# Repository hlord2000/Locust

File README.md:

# A Cricut Joy control board replacement
Reverse engineered from the 2019 Cricut Joy control board

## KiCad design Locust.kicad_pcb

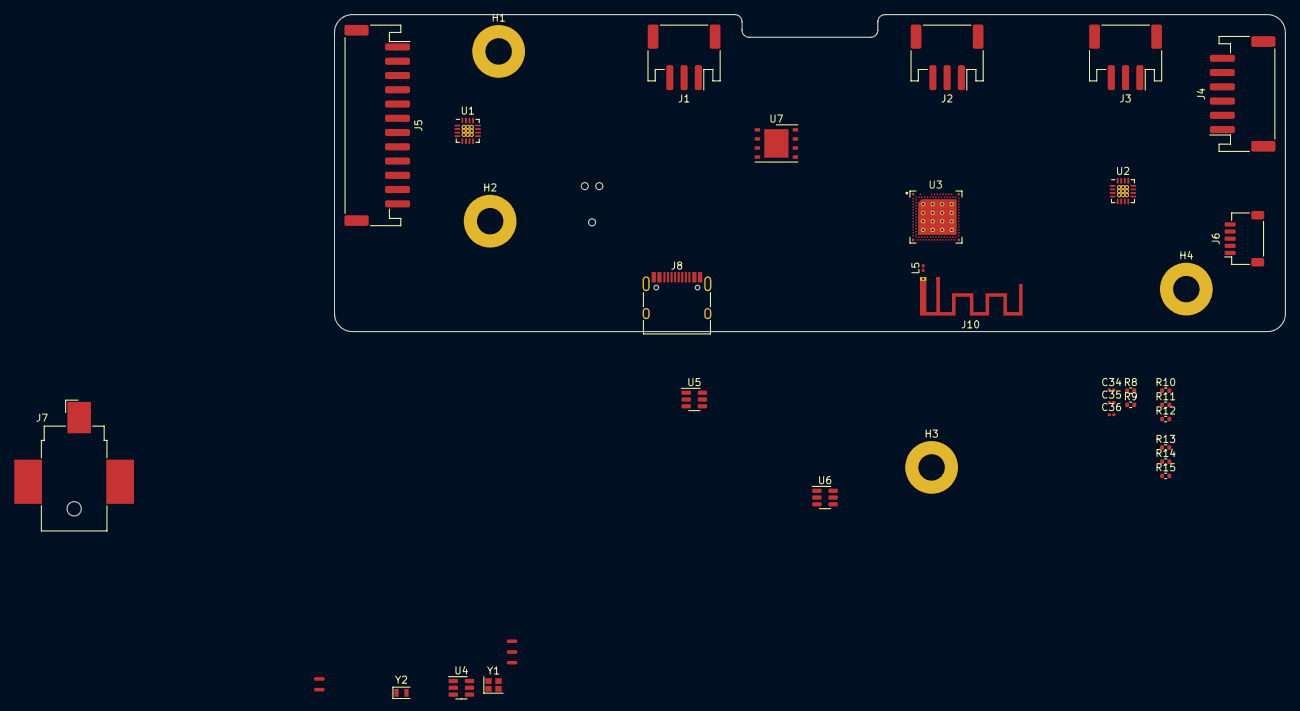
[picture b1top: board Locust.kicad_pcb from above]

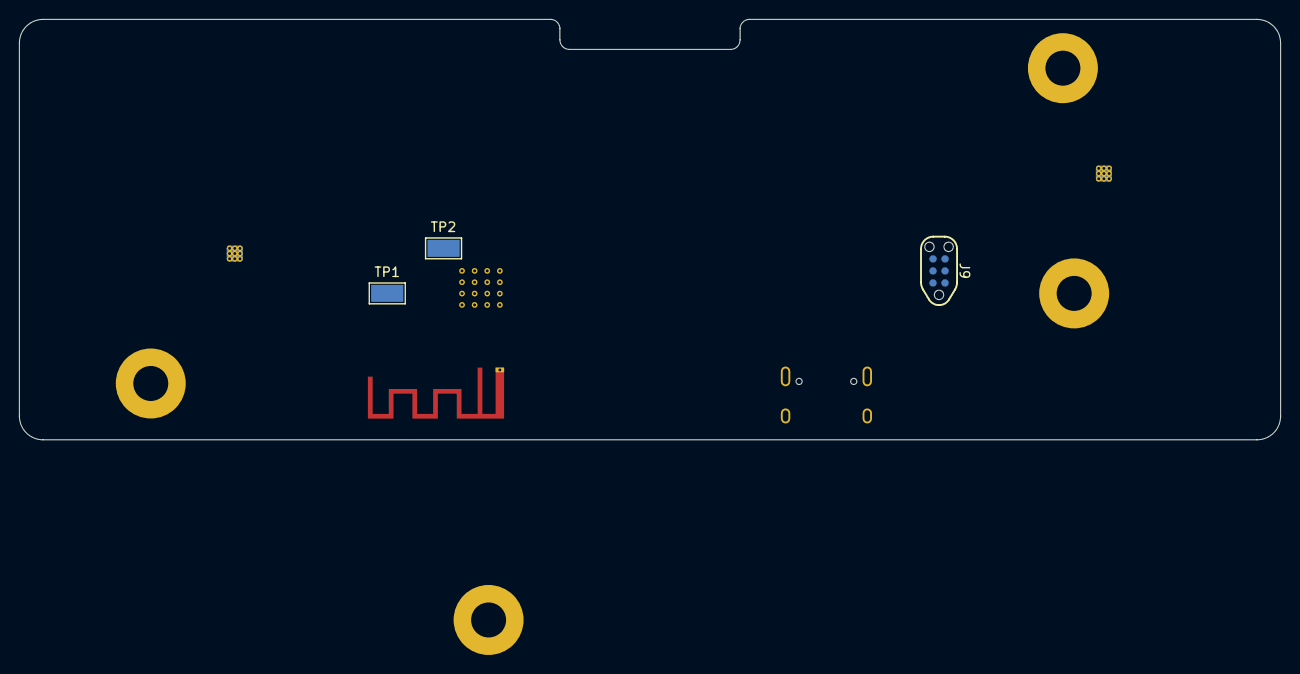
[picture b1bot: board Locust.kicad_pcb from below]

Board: 2 copper layers, 133.3 x 44.4 mm, 42 parts (3 on the bottom side), 37 nets, no tracks yet.

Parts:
C34: 0.7p; C_0201_0603Metric
C35: NC; C_0201_0603Metric
C36: 1u; L_0201_0603Metric
H1, H2, H3, H4: MountingHole_Pad; MountingHole_3.7mm_Pad
J1, J2, J3: JST PH S3B; JST_PH_S3B-PH-SM4-TB_1x03-1MP_P2.00mm_Horizontal
J4: Conn_01x06_MountingPin; JST_PH_S6B-PH-SM4-TB_1x06-1MP_P2.00mm_Horizontal
J5: Conn_01x12_MountingPin; JST_PH_S12B-PH-SM4-TB_1x12-1MP_P2.00mm_Horizontal
J6: Conn_01x05_MountingPin; JST_SH_SM05B-SRSS-TB_1x05-1MP_P1.00mm_Horizontal
J7: Barrel_Jack_MountingPin; BarrelJack_CUI_PJ-036AH-SMT_Horizontal
J8: USB_C_Receptacle_USB2.0; USB_C_Receptacle_HRO_TYPE-C-31-M-12
J9: TC2030_SWD; CON_TC2030_outlined
J10: Conn_01x02; Texas_SWRA117D_2.4GHz_Left
L5: 2.2n; L_0201_0603Metric
NT1, NT2, NT3, NT4, NT5: NetTie_2; NetTie-2_SMD_Pad0.5mm
R8, R9: 5.1k; R_0402_1005Metric
R10, R11, R12, R13, R14, R15: 100k; R_0402_1005Metric
TP1: UART_TX; TestPoint_Keystone_5015_Micro-Minature
TP2: UART_RX; TestPoint_Keystone_5015_Micro-Minature
U1, U2: DRV8847RTE; QFN-16-1EP_3x3mm_P0.5mm_EP1.7x1.7mm_ThermalVias
U3: nRF5340-QKXX; aQFN-94_7x7mm
U4: USBLC6-2SC6; SOT-23-6
U5: AP63203WU; TSOT-23-6
U6: AP63205WU; TSOT-23-6
U7: MX25L3233FZN; WSON-8-1EP_6x5mm_P1.27mm_EP3.4x4mm
Y1: 32MHz; Crystal_SMD_2016-4Pin_2.0x1.6mm
Y2: 32.768kHz; Crystal_SMD_2012-2Pin_2.0x1.2mm

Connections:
+3.3V: J1.1, J3.1, J6.1, J9.1 (VCC), NT4.2, NT5.2
+18V: NT1.2, NT2.2, U5.2 (EN), U5.3 (IN), U6.2 (EN), U6.3 (IN)
/MCU/D+: J8.A6 (D+), J8.B6 (D+), U3.B2 (D+), U4.1 (I/O1), U4.6 (I/O1)
/MCU/D-: J8.A7 (D-), J8.B7 (D-), U3.B4 (D-), U4.3 (I/O2), U4.4 (I/O2)
/MCU/SCK: U3.AK12 (P0.17/SCK), U7.6 (SCLK)
/MCU/SWCLK: J9.4 (SWCLK), U3.W31 (SWDCLK)
/MCU/SWDIO: J9.2 (SWDIO), U3.AA31 (SWDIO)
/MCU/~CS: U3.AK14 (P0.18/~CS), U7.1 (~CS)
/MCU/~RST: J9.3 (~RST), U3.AC31 (~RESET)
/Motors_Encoders/MOTOR_1+: J4.1, U2.16 (OUT1)
/Motors_Encoders/MOTOR_1-: J4.2, U2.2 (OUT2)
/Motors_Encoders/MOTOR_2+: J5.1, U1.16 (OUT1)
/Motors_Encoders/MOTOR_2-: J5.2, U1.2 (OUT2)
/Motors_Encoders/MOTOR_3+: J5.7, U1.5 (OUT3)
/Motors_Encoders/MOTOR_3-: J5.8, U1.3 (OUT4)
GND: C34.2, C35.2, C36.2, H1.1, H2.1, H3.1, H4.1, J1.3, J1.MP (MountPin), J2.3, J2.MP (MountPin), J3.3, J3.MP (MountPin), J4.3, J4.MP (MountPin), J5.3, J5.9, J5.MP (MountPin), J6.5, J6.MP (MountPin), J7.2, J8.A1 (GND), J8.A12 (GND), J8.B1 (GND), J8.B12 (GND), J8.S1 (SHIELD), J9.5 (GND), J10.1, R8.2, R9.2, R10.2, R11.2, R12.2, R13.2, R14.2, R15.2, U1.11 (GND), U1.17 (PPAD), U2.11 (GND), U2.17 (PPAD), U3.104 (VSS), U4.2 (GND), U5.4 (GND), U6.4 (GND), U7.4 (GND), U7.9 (EP), Y1.2, Y1.4
unnamed: J8.A5 (CC1), R8.1
unnamed: J8.B5 (CC2), R9.1
unnamed: C35.1, J10.2, L5.1
unnamed: NT1.1, U1.10 (VM)
unnamed: NT2.1, U2.10 (VM)
unnamed: C34.1, L5.2, U3.L31 (ANT)
unnamed: U3.N1 (P0.00/XL1), Y2.2
unnamed: U3.R1 (P0.01/XL2), Y2.1
unnamed: U3.AL5 (P0.13/IO0), U7.5 (SI/SIO0)
unnamed: U3.AK8 (P0.14/IO1), U7.2 (SO/SIO1)
unnamed: U3.AK10 (P0.15/IO2), U7.3 (~WP/SIO2)
unnamed: U3.AL9 (P0.16/IO3), U7.7 (~HOLD/SIO3)
unnamed: TP1.1, U3.AL13 (P0.19)
unnamed: TP2.1, U3.AK16 (P0.20)
unnamed: U3.C31 (XC1), Y1.1
unnamed: U3.B30 (XC2), Y1.3
unnamed: U3.A27 (DECR), U3.G31 (DECRF)
unnamed: NT3.1, U3.A5 (VBUS)
unnamed: NT4.1, U3.A19 (VDD), U3.AC1 (VDD), U3.AG1 (VDD), U3.AJ31 (VDD), U3.AL3 (VDD), U3.AL7 (VDD), U3.AL11 (VDD), U3.AL17 (VDD), U3.AL25 (VDD), U3.B8 (VDD), U3.B28 (VDD), U3.C1 (VDD), U3.E1 (VDDH), U3.E31 (VDD), U3.L1 (VDD), U3.N31 (VDD), U3.U1 (VDD)
unnamed: C36.1, NT5.1, U7.8 (VCC)
VBUS_ESD: J8.A4 (VBUS), J8.A9 (VBUS), J8.B4 (VBUS), J8.B9 (VBUS), U4.5 (VBUS)

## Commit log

2023-10-04 Initial commit.
2023-10-04 Added KiCAD Files
2023-10-07 Added nrf5340 and pi filters on output of switching supplies
2023-10-10 10/09/23 - Schematic v0.1
2023-10-10 Modified README, added image, fixed schematic
2023-10-10 Create LICENSE
